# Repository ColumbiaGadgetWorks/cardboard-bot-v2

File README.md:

# Cardboard Bot v2

Cardboard battlebots for Columbia Gadget Works, built on the Seeed XIAO ESP32-C3.

- Each robot hosts its own Wi-Fi access point. You drive it from a phone browser,
  with an optional Bluetooth gamepad (DS4 and others) through the browser's Gamepad API.
- Firmware is flashed from a browser-based web flasher on GitHub Pages; updates go over the
  robot's own AP.
- The board runs from a 2S or 3S LiPo on a screw terminal, drives two gearmotors through two
  DRV8870s, and has three 3-pin outputs for ESCs or servos (two weapon ESCs by default).

| Folder | Contents |
|---|---|
| [`hardware/`](hardware/) | KiCad 7 main board, rev B (2S/3S LiPo, 60 × 46 mm): schematic, PCB, JLCPCB fab files and the generator scripts |
| [`firmware/`](firmware/) | ESP-IDF firmware for the XIAO ESP32-C3, including the phone controller page |
| [`site/`](site/) | Web flasher, published to GitHub Pages with every firmware build |

**Flash a robot:** <https://columbiagadgetworks.github.io/cardboard-bot-v2/> (desktop Chrome or Edge, or Firefox 151+).
**Drive it:** join the robot's Wi-Fi (`CGW-<name>`) and open **https://192.168.4.1** on the phone.

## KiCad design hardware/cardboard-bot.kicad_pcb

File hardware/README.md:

# Cardboard Bot v2 – main board (rev B)

60 × 46 mm, 2-layer, 2 oz copper, for a **2S or 3S LiPo** on a screw terminal. JLCPCB assembles
the SMD parts on the top side; CGW hand-solders the through-hole parts. Nothing goes on the back.

| What | Where |
|---|---|
| Schematic (PDF) | `docs/schematic.pdf` |
| KiCad 7 project | `cardboard-bot.kicad_pro` / `.kicad_sch` / `.kicad_pcb` |
| JLCPCB upload files | `fab/` (gerber zip, BOM, CPL) |
| Hand-solder list | `fab/cardboard-bot-v2-revB-hand-solder.csv` |
| Part-number check list | `docs/BOM_CHECK.md` |

## What's on the board

Parts were picked for JLC stock: Basic or no-fee Preferred parts wherever JLC has one, otherwise a
well-stocked Extended part (stock checked 28 Oct 2026, see `docs/BOM_CHECK.md`). Everything on the
battery side is rated above 3S (12.6 V full).

- **Battery input:** 5.08 mm screw terminal J1 (top-left), then a **20 A mini blade fuse**, then two
  wire pads for an off-board **power switch** (10 A+ DC, 18 AWG). A unidirectional **SMAJ13A**
  clamps spikes at about 21 V; a reversed battery makes it conduct and blows the fuse.
- **ESC power:** two 5.08 mm screw terminals on the right edge (ESC 1, ESC 2), after the fuse
  and switch, with a 470 µF / 25 V bulk capacitor next to them.
- **Drive:** two **DRV8870** H-bridges (6.5–45 V, 3.6 A peak), one per motor, each next to its
  3.5 mm motor terminal: **LEFT MOTOR** on the left edge, **RIGHT MOTOR** on the right edge.
  0.1 Ω sense resistors and VREF = 2.53 V limit each motor to about 2.5 A. The DRV8870 stops
  below about 6.5 V, so on 2S the drive cuts out near empty (the firmware stops it at 3.0 V/cell anyway).
- **5 V:** TPS54202 buck (28 V max in) behind a Schottky diode and a 470 µF / 25 V hold-up
  capacitor, so ESC current spikes can't reset the ESP32. A second Schottky feeds the XIAO, so
  plugging in its USB while the robot is on is safe.
- **Outputs:** three 3-pin headers (GND / V+ / SIG): OUT1 (GPIO10), OUT2 (GPIO20), OUT3 (GPIO21).
  V+ is 5 V through a Schottky per output, so an ESC's BEC can't back-feed the board. The
  firmware default is two weapon ESCs on OUT1 and OUT2. OUT3's pin carries the ESP32 boot
  messages for a moment at power-up, so use it for a servo rather than an ESC.
- **Pull-downs:** 10k on all four motor inputs and all three outputs, so the motors coast and the
  ESCs see "off" while the ESP32 resets and boots (its pins float until the firmware starts).
- **Battery sense:** pack ÷ 6 (100k / 20k) on GPIO3, so 3S full (12.6 V) reads 2.1 V. The
  firmware detects 2S / 3S at power-on.
- **Status LED:** pads for one LED cut from a WS2812B strip (5 V, 60 LED/m, 10 mm), powered
  through a 1N4148W (about 4.2 V) so the 3.3 V data line is read reliably.
- **I2C header** J2 (GND, 3V3, SCL, SDA) with pull-ups, for add-ons.
- **Mounting:** two M3 holes (left middle, bottom right).

### XIAO pin map

| XIAO | GPIO | Use |
|---|---|---|
| D0 | 2 | SDA (I2C header) |
| D1 | 3 | Battery sense (pack ÷ 6) |
| D2 / D3 | 4 / 5 | Left DRV8870 IN1 / IN2 |
| D4 / D5 | 6 / 7 | Right DRV8870 IN1 / IN2 |
| D6 | 21 | OUT3 – also UART TX at boot |
| D7 | 20 | OUT2 |
| D8 | 8 | SCL (I2C header) |
| D9 | 9 | RGB LED data (BOOT button pin) |
| D10 | 10 | OUT1 |

GPIO2, GPIO8 and GPIO9 are strapping pins. They only carry signals that idle high at boot
(I2C pull-ups, and the BOOT button with the LED data line), so the chip always boots normally.
None of them has a pull-down.

## Before ordering – check these

1. **LCSC part numbers and stock.** Go through `docs/BOM_CHECK.md` on jlcpcb.com/parts.
2. **JLC placement preview.** `ROT_FIX` in `gen/fab.py` holds the corrections from rev A's preview.
   The DRV8870 (U3, U4) is new: check its pin-1 dot against the silkscreen triangle and add a
   correction if it's turned. JLC flags U1's footprint name (TSOT-23-6 vs SOT-23-6); the pads match.
3. **Values to sanity-check against the datasheets:** DRV8870 VREF / sense resistor (2.5 A limit),
   TPS54202 output inductor (10 µH) and capacitors (2 × 22 µF).
4. **Assembly:**
   - **LED strip:** cut one LED from the strip on the cut lines. Tin the three J10 pads, lay the
     piece on them with its DIN end on the +5V / DIN / GND pads (arrow pointing away), and heat
     each strip pad from the top. Strips differ: check the +5V / DIN / GND order matches the
     silkscreen first, or wire it with three short wires instead.
   - **Power switch:** mount it in the cardboard and run two 18 AWG wires to the SW1 pads.
   - **Battery:** use 14–16 AWG leads into J1. The 5.08 mm terminals are rated about 16 A; for
     bigger weapons, solder the battery leads instead.

## Regenerating

Everything is generated from `gen/circuit.py` (parts, LCSC numbers, nets).
You need KiCad 7 (`kicad-cli` and its Python module), python3-numpy and python3-pil.

```sh
python3 gen/gen_footprints.py          # lib/cgw.pretty (XIAO socket, LED strip pads, CGW logos)
python3 gen/gen_sch.py                 # schematic + lib/cgw.kicad_sym
kicad-cli sch export pdf -o docs/schematic.pdf cardboard-bot.kicad_sch
PY=/usr/bin/python3.12
$PY gen/gen_pcb.py                     # outline, placement, silkscreen, pre-routed power copper, router keepouts
$PY gen/route.py --stage zones         # GND pours (both layers) + solid power pours
$PY gen/fixroute.py                    # A* grid router for every remaining connection (rips up and retries)
$PY gen/route.py --stage stitch        # GND stitching vias
$PY gen/islands.py                     # ties any leftover GND pour islands
$PY gen/gnd_check.py                   # lists GND copper cut off from the main cluster (DRC won't say where)
(cd gen && $PY tie_pad.py --min 3 REF PAD)   # route a stranded pad to a GND via, if gnd_check finds one
$PY gen/route.py --stage drop-keepouts && $PY gen/route.py --stage fill
$PY gen/silk.py                        # redraw labels only (safe on a routed board)
$PY gen/drc.py                         # DRC summary
python3 gen/fab.py                     # fab/ outputs; BOM and CPL designators are cross-checked
bash gen/render.sh                     # PNG previews
```

`gen_pcb.py` builds the board from scratch, which wipes the routing. A full re-route takes a few
minutes. After small changes it is usually easier to edit `cardboard-bot.kicad_pcb` in KiCad directly.
`gen/patch_prewire.py NET,...` re-applies the fixed copper of individual nets on a routed board.

This board was routed with `gen/fixroute.py`. `gen/route.py` can also run Freerouting if you have
Java and `freerouting.jar` installed (`route.py` with no arguments).

## Preview

| Top | Bottom (mirrored) |
|---|---|
|  |  |

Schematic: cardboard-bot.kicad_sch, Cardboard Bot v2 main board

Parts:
C1, C2: 470uF 25V; CP_Radial_D8.0mm_P3.50mm; MPN 470uF 25V radial, 8 mm dia, 3.5 mm pitc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
C3, C9, C14, C16: 10uF; C_0805_2012Metric; MPN CL21A106KAYNNNE; LCSC C15850
C4, C5, C10, C11, C12, C13, C15, C17, C18: 100nF; C_0603_1608Metric; MPN CC0603KRX7R9BB104; LCSC C14663
C6, C7: 22uF; C_0805_2012Metric; MPN CL21A226MAQNNNE; LCSC C45783
D1: SMAJ13A; D_SMA; MPN SMAJ13A; LCSC C19077533
D2: SS34; D_SMA; MPN SS34; LCSC C8678
D3: B5819W; D_SOD-123; MPN B5819W SL; LCSC C8598
D4, D5, D6: 1N5819WS; D_SOD-323; MPN 1N5819WS; LCSC C191023
D7: 1N4148W; D_SOD-123; MPN 1N4148W; LCSC C81598
F1: 20A mini blade; Fuseholder_Blade_Mini_Keystone_3568; MPN Mini blade holder (Keystone 3568 footpr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
J1: BATTERY; TerminalBlock_Phoenix_MKDS-1,5-2-5.08_1x02_P5.08mm_Horizont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; MPN 2P screw terminal 5.08mm (KF301), 2S or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
J2: I2C; PinSocket_1x04_P2.54mm_Vertical; MPN 1x4 female header 2.54
J3: LEFT MOTOR; TerminalBlock_Phoenix_PT-1,5-2-3.5-H_1x02_P3.50mm_Horizontal; MPN 2P screw terminal 3.5mm
J4: RIGHT MOTOR; TerminalBlock_Phoenix_PT-1,5-2-3.5-H_1x02_P3.50mm_Horizontal; MPN 2P screw terminal 3.5mm
J5: OUT1; PinHeader_1x03_P2.54mm_Vertical; MPN 1x3 male header 2.54
J6: OUT2; PinHeader_1x03_P2.54mm_Vertical; MPN 1x3 male header 2.54
J7: OUT3; PinHeader_1x03_P2.54mm_Vertical; MPN 1x3 male header 2.54
J8: ESC PWR 1; TerminalBlock_Phoenix_MKDS-1,5-2-5.08_1x02_P5.08mm_Horizont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; MPN 2P screw terminal 5.08mm (KF301)
J9: ESC PWR 2; TerminalBlock_Phoenix_MKDS-1,5-2-5.08_1x02_P5.08mm_Horizont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; MPN 2P screw terminal 5.08mm (KF301)
J10: LED STRIP; WS2812B_Strip_1LED; MPN 1 LED cut from a WS2812B strip: 5 V, 60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
L1: 10uH 2.35A; L_Cenker_CKCS4030; MPN FHD4020S-100MT; LCSC C602032
R1: 75k; R_0603_1608Metric; MPN 0603WAF7502T5E; LCSC C23242
R2, R9, R11, R12, R13, R14, R18, R19, R20: 10k; R_0603_1608Metric; MPN 0603WAF1002T5E; LCSC C25804
R3, R4: 4.7k; R_0603_1608Metric; MPN 0603WAF4701T5E; LCSC C23162
R5: 100k; R_0603_1608Metric; MPN 0603WAF1003T5E; LCSC C25803
R6: 20k; R_0603_1608Metric; MPN 0603WAF2002T5E; LCSC C4184
R7, R8: 0.1R; R_1206_3216Metric; MPN 1206W4F100LT5E; LCSC C25334
R10: 33k; R_0603_1608Metric; MPN 0603WAF3302T5E; LCSC C4216
R15, R16, R17: 1k; R_0603_1608Metric; MPN 0603WAF1001T5E; LCSC C21190
R21: 330R; R_0603_1608Metric; MPN 0603WAF3300T5E; LCSC C23138
SW1: POWER SW; SolderWire-0.75sqmm_1x02_P4.8mm_D1.25mm_OD2.3mm; MPN SPST rocker or toggle, 10 A+ at 16 V DC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
TP1: +3V3; TestPoint_Pad_D1.5mm
TP2: GND; TestPoint_Pad_D1.5mm
U1: TPS54202DDCR; TSOT-23-6; MPN TPS54202DDCR; LCSC C191884
U2: XIAO ESP32-C3; XIAO_Socket; MPN Seeed XIAO ESP32C3 + 2x 1x7 female head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
U3, U4: DRV8870DDAR; Texas_HTSOP-8-1EP_3.9x4.9mm_P1.27mm_EP2.95x4.9mm_Mask2.4x3.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; MPN DRV8870DDAR; LCSC C86590

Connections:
+3V3: C11.1, J2.2, R3.1, R4.1, R9.1, TP1.1, U2.12 (3V3)
+5V: C6.1, C7.1, D3.2 (A), D4.2 (A), D5.2 (A), D6.2 (A), D7.2 (A), L1.2, R1.1
+5V_XIAO: C9.1, C10.1, D3.1 (K), U2.14 (5V)
AIN1: R11.1, U2.3 (D2/GPIO4), U3.3 (IN1)
AIN2: R12.1, U2.4 (D3/GPIO5), U3.2 (IN2)
BAT+: F1.1, J1.1
BIN1: R13.1, U2.5 (D4/GPIO6), U4.3 (IN1)
BIN2: R14.1, U2.6 (D5/GPIO7), U4.2 (IN2)
BUCK_BST: C5.1, U1.6 (BOOT)
BUCK_FB: R1.2, R2.1, U1.4 (FB)
BUCK_SW: C5.2, L1.1, U1.2 (SW)
DRV_VREF: C13.1, R9.2, R10.1, U3.4 (VREF), U4.4 (VREF)
GND: C1.2, C2.2, C3.2, C4.2, C6.2, C7.2, C9.2, C10.2, C11.2, C12.2, C13.2, C14.2, C15.2, C16.2, C17.2, C18.2, D1.2 (A), J1.2, J2.1, J5.1, J6.1, J7.1, J8.2, J9.2, J10.3, R2.2, R6.2, R7.2, R8.2, R10.2, R11.2, R12.2, R13.2, R14.2, R18.2, R19.2, R20.2, TP2.1, U1.1 (GND), U2.13 (GND), U3.1 (GND), U3.9 (GND), U4.1 (GND), U4.9 (GND)
IO10: R15.1, R18.1, U2.11 (D10/GPIO10)
IO20: R16.1, R19.1, U2.8 (D7/GPIO20)
IO21: R17.1, R20.1, U2.7 (D6/GPIO21)
ISEN_L: R7.1, U3.7 (ISEN)
ISEN_R: R8.1, U4.7 (ISEN)
LED_DIN: J10.2, R21.2
LED_DIN3: R21.1, U2.10 (D9/GPIO9)
LED_VDD: C18.1, D7.1 (K), J10.1
MOTL_A: J3.1, U3.6 (OUT1)
MOTL_B: J3.2, U3.8 (OUT2)
MOTR_A: J4.1, U4.6 (OUT1)
MOTR_B: J4.2, U4.8 (OUT2)
OUT1_SIG: J5.3, R15.2
OUT1_VP: D4.1 (K), J5.2
OUT2_SIG: J6.3, R16.2
OUT2_VP: D5.1 (K), J6.2
OUT3_SIG: J7.3, R17.2
OUT3_VP: D6.1 (K), J7.2
SCL: J2.3, R4.2, U2.9 (D8/GPIO8)
SDA: J2.4, R3.2, U2.1 (D0/GPIO2)
VBAT_SNS: C12.1, R5.2, R6.1, U2.2 (D1/GPIO3)
VFUSE: F1.2, SW1.1 (A)
VHOLD: C2.1, C3.1, C4.1, D2.1 (K), U1.3 (VIN)
VSYS: C1.1, C14.1, C15.1, C16.1, C17.1, D1.1 (K), D2.2 (A), J8.1, J9.1, R5.1, SW1.2 (B), U3.5 (VM), U4.5 (VM)

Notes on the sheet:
1 Battery input (2S / 3S LiPo), 20 A blade fuse, power switch, surge clamp, ESC power
2 Hold-up + 5 V buck (TPS54202), XIAO feed
3 XIAO ESP32-C3, I2C, battery sense
4 2x DRV8870 drive, 2.5 A current limit
5 PWM outputs (ESC or servo)
6 RGB status LED (WS2812B strip piece)
Power flags (ERC)
Cardboard Bot v2 main board - rev B - Columbia Gadget Works
Generated from hardware/gen/circuit.py (do not hand-edit; edit circuit.py and regenerate).
All connections are made by net labels at pin ends.
Power: 2S or 3S LiPo on J1. Everything on VSYS is rated for 3S (12.6 V) with margin; SMAJ13A clamps spikes at about 21 V.
XIAO pins: D0 SDA(GPIO2) D1 VBAT/6(GPIO3) D2-D3 left DRV8870 IN1/IN2 D4-D5 right DRV8870 IN1/IN2 D6 OUT3(GPIO21) D7 OUT2(GPIO20) D8 SCL(GPIO8) D9 LED(GPIO9) D10 OUT1(GPIO10)
10k pull-downs on every motor input and output keep motors and ESCs off while the ESP32 boots.

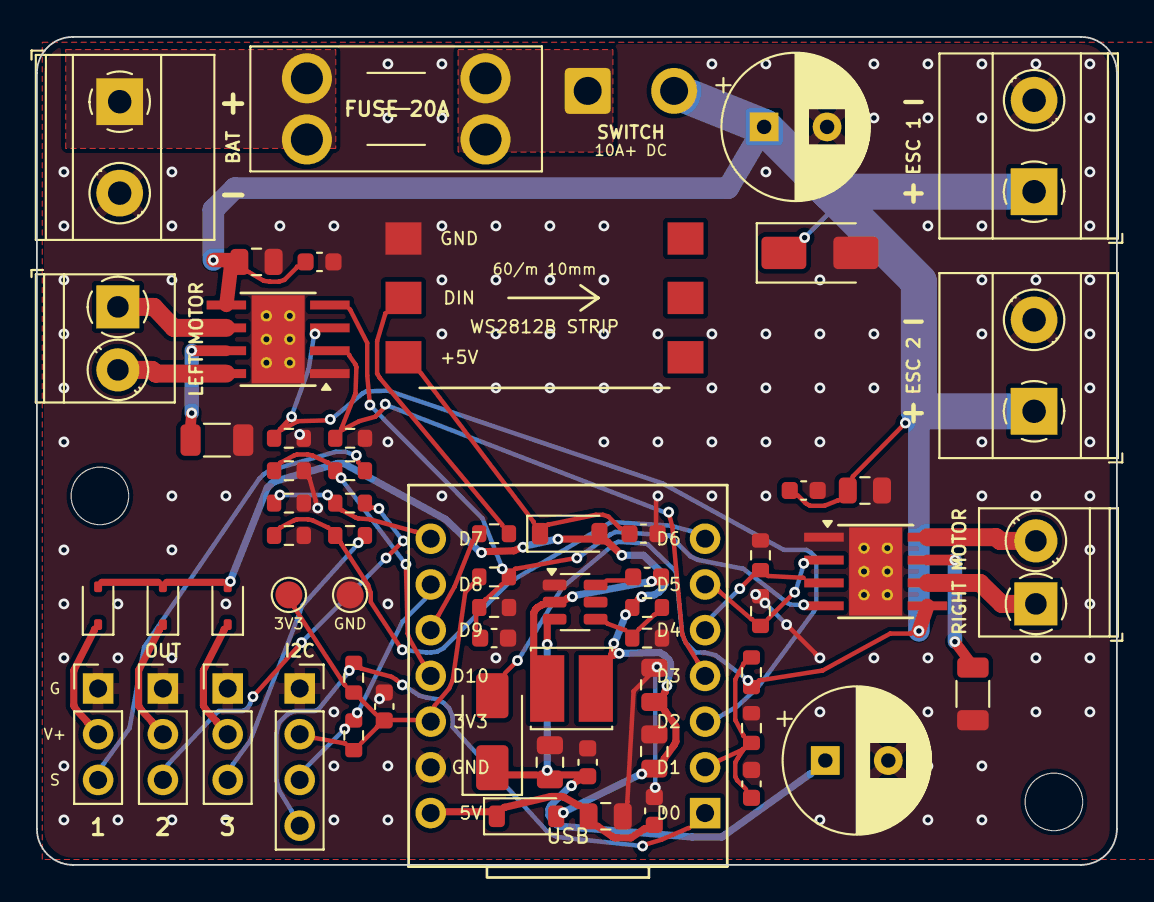
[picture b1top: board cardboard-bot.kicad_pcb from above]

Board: 2 copper layers, 60.0 x 46.0 mm, 67 parts (1 on the bottom side), 37 nets.

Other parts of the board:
H1, H2: MountingHole_3.2mm_M3
LOGO2: CGW_Logo

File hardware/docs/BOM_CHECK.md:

# LCSC part check (rev B)

Stock, price and library type are from a JLC parts snapshot taken **28 Oct 2026**:
- [yaqwsx/jlcparts](https://github.com/yaqwsx/jlcparts) for stock and price
- [CDFER/jlcpcb-parts-database](https://github.com/CDFER/jlcpcb-parts-database) for the Basic and Preferred lists

They change daily. Open each part on <https://jlcpcb.com/parts> before ordering and tick it off.

- **Basic** and **Preferred** parts have no feeder fee.
- Each **Extended** line usually adds about $3 per order.
- JLC stocks no Basic motor driver, buck converter or power inductor, so those three are
  well-stocked Extended parts. There is no Basic TVS with a stand-off above 3S, so D1 is the
  SMAJ13A (Preferred).

## 3S ratings

| Part | Rating | On the 12.6 V rail |
|---|---|---|
| DRV8870 (U3, U4) | 45 V | motor supply |
| TPS54202 (U1) | 28 V | buck input |
| SMAJ13A (D1) | 13 V stand-off, clamps 21.5 V | surge clamp |
| SS34 (D2) | 40 V | hold-up diode |
| 10 µF 0805 (C3, C14, C16) | 25 V | bulk ceramics |
| 100 nF 0603 | 50 V | decoupling |
| 470 µF radials (C1, C2) | 25 V | bulk, hand-soldered |

## Check by hand before paying

- **U3, U4 DRV8870DDAR:** pin 1 GND, 2 IN2, 3 IN1, 4 VREF, 5 VM, 6 OUT1, 7 ISEN, 8 OUT2, pad GND
  (TI SLVSCY9). Check the pin-1 dot in JLC's placement preview; this part is new on rev B.
- **Rotations:** `ROT_FIX` in `gen/fab.py` holds the rev A corrections (U1 TPS54202 is the same part).
- **U1 footprint warning:** JLC lists the TPS54202DDCR as SOT-23-6; the board uses KiCad's TSOT-23-6,
  which is TI's DDC land pattern (same pin pitch and pad positions). The warning is about the name only.

## Assembled by JLCPCB (top side)

| LCSC | Value | MPN | Footprint | Qty/board | Designators | JLC library | JLC stock | Unit price |
|---|---|---|---|---|---|---|---|---|
| C15850 | 10uF | CL21A106KAYNNNE | C_0805_2012Metric | 4 | C14, C16, C3, C9 | Basic | 3,710,191 | $0.0692 |
| C14663 | 100nF | CC0603KRX7R9BB104 | C_0603_1608Metric | 9 | C10, C11, C12, C13, C15, C17, C18, C4, C5 | Basic | 50,349,394 | $0.0141 |
| C45783 | 22uF | CL21A226MAQNNNE | C_0805_2012Metric | 2 | C6, C7 | Basic | 3,360,923 | $0.2384 |
| C19077533 | SMAJ13A | SMAJ13A | D_SMA | 1 | D1 | Preferred (no fee) | 45,855 | $0.0382 |
| C8678 | SS34 | SS34 | D_SMA | 1 | D2 | Basic | 4,004,526 | $0.0351 |
| C8598 | B5819W | B5819W SL | D_SOD-123 | 1 | D3 | Basic | 384,842 | $0.0284 |
| C191023 | 1N5819WS | 1N5819WS | D_SOD-323 | 3 | D4, D5, D6 | Basic | 4,286,668 | $0.0139 |
| C81598 | 1N4148W | 1N4148W | D_SOD-123 | 1 | D7 | Basic | 4,633,707 | $0.0124 |
| C602032 | 10uH 2.35A | FHD4020S-100MT | L_Cenker_CKCS4030 | 1 | L1 | Extended ($3 fee) | 99,381 | $0.0640 |
| C23242 | 75k | 0603WAF7502T5E | R_0603_1608Metric | 1 | R1 | Basic | 1,012,894 | $0.0021 |
| C4216 | 33k | 0603WAF3302T5E | R_0603_1608Metric | 1 | R10 | Basic | 3,644,037 | $0.0021 |
| C21190 | 1k | 0603WAF1001T5E | R_0603_1608Metric | 3 | R15, R16, R17 | Basic | 24,277,749 | $0.0020 |
| C25804 | 10k | 0603WAF1002T5E | R_0603_1608Metric | 9 | R11, R12, R13, R14, R18, R19, R2, R20, R9 | Basic | 32,380,385 | $0.0052 |
| C23138 | 330R | 0603WAF3300T5E | R_0603_1608Metric | 1 | R21 | Basic | 3,527,043 | $0.0022 |
| C23162 | 4.7k | 0603WAF4701T5E | R_0603_1608Metric | 2 | R3, R4 | Basic | 19,500,720 | $0.0028 |
| C25803 | 100k | 0603WAF1003T5E | R_0603_1608Metric | 1 | R5 | Basic | 19,748,113 | $0.0031 |
| C4184 | 20k | 0603WAF2002T5E | R_0603_1608Metric | 1 | R6 | Basic | 7,868,484 | $0.0022 |
| C25334 | 0.1R | 1206W4F100LT5E | R_1206_3216Metric | 2 | R7, R8 | Basic | 552,267 | $0.0091 |
| C191884 | TPS54202DDCR | TPS54202DDCR | TSOT-23-6 | 1 | U1 | Extended ($3 fee) | 299,988 | $0.1786 |
| C86590 | DRV8870DDAR | DRV8870DDAR | Texas_HTSOP-8-1EP_3.9x4.9mm_P1.27mm_EP2.95x4.9mm_Mask2.4x3.1mm_ThermalVias | 2 | U3, U4 | Extended ($3 fee) | 158,471 | $0.3456 |

**20 BOM lines.** Basic: 16, Preferred: 1, Extended: 3 (about $9 in feeder fees per order, if JLC charges them).
Parts cost about **$2.06 per board** at single-unit prices, so about $62 for 30 boards, before JLC's setup and assembly fees.

## Hand-soldered by CGW

| Designator | Part | Notes |
|---|---|---|
| J1 | BATTERY | 2P screw terminal 5.08mm (KF301), 2S or 3S LiPo |
| F1 | 20A mini blade | Mini blade holder (Keystone 3568 footprint) |
| SW1 | POWER SW | SPST rocker or toggle, 10 A+ at 16 V DC, panel mount, 18 AWG silicone wire |
| C1 | 470uF 25V | 470uF 25V radial, 8 mm dia, 3.5 mm pitch, low ESR |
| J8 | ESC PWR 1 | 2P screw terminal 5.08mm (KF301) |
| J9 | ESC PWR 2 | 2P screw terminal 5.08mm (KF301) |
| C2 | 470uF 25V | 470uF 25V radial, 8 mm dia, 3.5 mm pitch, low ESR |
| U2 | XIAO ESP32-C3 | Seeed XIAO ESP32C3 + 2x 1x7 female header |
| J2 | I2C | 1x4 female header 2.54 |
| J3 | LEFT MOTOR | 2P screw terminal 3.5mm |
| J4 | RIGHT MOTOR | 2P screw terminal 3.5mm |
| J5 | OUT1 | 1x3 male header 2.54 |
| J6 | OUT2 | 1x3 male header 2.54 |
| J7 | OUT3 | 1x3 male header 2.54 |
| J10 | LED STRIP | 1 LED cut from a WS2812B strip: 5 V, 60 LED/m, 10 mm wide, pads +5V/DIN/GND |

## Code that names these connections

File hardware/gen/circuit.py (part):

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         pins={"1": BAT, "2": GND}))
add(dict(ref="F1", sym="Device:Fuse", value="20A mini blade", fp="Fuse:Fuseholder_Blade_Mini_Keystone_3568",
         lcsc="", mpn="Mini blade holder (Keystone 3568 footprint)", place="hand", block="power",
         pins={"1": BAT, "2": VFUSE}))
# The power switch carries the full battery current, so it's an off-board panel switch on two
# 0.75 mm2 (18 AWG) wire pads (fuse output -> VSYS).
add(dict(ref="SW1", sym="Switch:SW_SPST", value="POWER SW", fp="Connector_Wire:SolderWire-0.75sqmm_1x02_P4.8mm_D1.25mm_OD2.3mm",
         lcsc="", mpn="SPST rocker or toggle, 10 A+ at 16 V DC, panel mount, 18 AWG silicone wire",
         place="hand", block="power", pins={"1": VFUSE, "2": VSYS}))
# 13 V stand-off (3S is 12.6 V full), clamps 21.5 V: below the buck's 28 V and the 25 V capacitors.
# Unidirectional, so a reversed battery forward-biases it and blows the fuse.
add(dict(ref="D1", sym="Device:D_Zener", value="SMAJ13A", fp="Diode_SMD:D_SMA",
         lcsc="C19077533", mpn="SMAJ13A", verified=True, place="jlc", block="power",
         pins={"1": VSYS, "2": GND}))
add(CP("C1", "470uF 25V", VSYS, GND, fp=CP8, mpn=CP470_NOTE, place="hand", block="power"))
add(dict(ref="J8", sym="Connector_Generic:Conn_01x02", value="ESC PWR 1", fp=TERM508,
         lcsc="", mpn="2P screw terminal 5.08mm (KF301)", place="hand", block="power", pins={"1": VSYS, "2": GND}))
add(dict(ref="J9", sym="Connector_Generic:Conn_01x02", value="ESC PWR 2", fp=TERM508,
         lcsc="", mpn="2P screw terminal 5.08mm (KF301)", place="hand", block="power", pins={"1": VSYS, "2": GND}))

# ---------------------------------------------------------------------------
# 2. 5 V buck with hold-up, XIAO feed
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# TPS54202: 4.5-28 V in; EN floats = enabled (internal pull-up)
add(dict(ref="U1", sym="Regulator_Switching:TPS54202DDC", value="TPS54202DDCR", fp="Package_TO_SOT_SMD:TSOT-23-6",
         lcsc="C191884", mpn="TPS54202DDCR", verified=True, place="jlc", block="buck",
         pins={"1": GND, "2": "BUCK_SW", "3": VHOLD, "4": "BUCK_FB", "5": None, "6": "BUCK_BST"}))
add(C("C5", "100nF", "BUCK_BST", "BUCK_SW", block="buck", **C100N))
add(dict(ref="L1", sym="Device:L", value="10uH 2.35A", fp="Inductor_SMD:L_Cenker_CKCS4030",
         lcsc="C602032", mpn="FHD4020S-100MT", verified=True, place="jlc", block="buck",
         pins={"1": "BUCK_SW", "2": V5}))
add(R("R1", "75k", V5, "BUCK_FB", lcsc="C23242", mpn="0603WAF7502T5E", verified=True, block="buck"))   # 0.596 V x (1 + 75/10) = 5.07 V
add(R("R2", "10k", "BUCK_FB", GND, block="buck", **R10K))
add(C("C6", "22uF", V5, GND, fp=F0805C, block="buck", **C22U))
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# ---------------------------------------------------------------------------
add(dict(ref="U2", sym="cgw:XIAO_ESP32C3", value="XIAO ESP32-C3", fp="cgw:XIAO_Socket",
         lcsc="", mpn="Seeed XIAO ESP32C3 + 2x 1x7 female header", place="hand", block="mcu",
         pins={"1": "SDA",        # D0 GPIO2  (strap, pulled up)
               "2": "VBAT_SNS",   # D1 GPIO3  battery / 6
               "3": "AIN1",       # D2 GPIO4  left motor
               "4": "AIN2",       # D3 GPIO5
               "5": "BIN1",       # D4 GPIO6  right motor
               "6": "BIN2",       # D5 GPIO7
               "7": "IO21",       # D6 GPIO21 OUT3 (ROM boot log for a moment at power-up)
               "8": "IO20",       # D7 GPIO20 OUT2
               "9": "SCL",        # D8 GPIO8  (strap, pulled up)
               "10": "LED_DIN3",  # D9 GPIO9  RGB LED + BOOT button
               "11": "IO10",      # D10 GPIO10 OUT1
               "12": V3, "13": GND, "14": V5_XIAO}))
add(R("R3", "4.7k", V3, "SDA", lcsc="C23162", mpn="0603WAF4701T5E", verified=True, block="mcu"))
add(R("R4", "4.7k", V3, "SCL", lcsc="C23162", mpn="0603WAF4701T5E", verified=True, block="mcu"))
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add(dict(ref="J2", sym="Connector_Generic:Conn_01x04", value="I2C", fp="Connector_PinSocket_2.54mm:PinSocket_1x04_P2.54mm_Vertical",
         lcsc="", mpn="1x4 female header 2.54", place="hand", block="mcu",
         pins={"1": GND, "2": V3, "3": "SCL", "4": "SDA"}))
# Battery voltage on GPIO3 (ADC1 ch3): VSYS / 6 -> 2.1 V at 12.6 V (3S full)
add(R("R5", "100k", VSYS, "VBAT_SNS", block="mcu", **R100K))
add(R("R6", "20k", "VBAT_SNS", GND, block="mcu", **R20K))
add(C("C12", "100nF", "VBAT_SNS", GND, block="mcu", **C100N))
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        ("U4", "BIN1", "BIN2", "MOTR_A", "MOTR_B", "ISEN_R", "R8", "C16", "C17", "J4", "RIGHT MOTOR")):
    add(dict(ref=u, sym="Driver_Motor:DRV8870DDA", value=DRV, fp=DRV_FP,
             lcsc="C86590", mpn=DRV, verified=True, place="jlc", block="drive",
             pins={"1": GND, "2": b, "3": a, "4": "DRV_VREF", "5": VSYS, "6": oa, "7": isen, "8": ob, "9": GND}))
    add(R(rs, "0.1R", isen, GND, fp="Resistor_SMD:R_1206_3216Metric", lcsc="C25334",
          mpn="1206W4F100LT5E", verified=True, block="drive"))
    add(C(cb, "10uF", VSYS, GND, fp=F0805C, block="drive", **C10U))
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# WS2812B strip LED run from 5 V minus a diode (~4.2 V), so the ESP32's 3.3 V data meets VIH = 0.7 x VDD
add(dict(ref="D7", sym="Device:D", value="1N4148W", fp="Diode_SMD:D_SOD-123",
         lcsc="C81598", mpn="1N4148W", verified=True, place="jlc", block="led",
         pins={"1": "LED_VDD", "2": V5}))
add(R("R21", "330R", "LED_DIN3", "LED_DIN", block="led", **R330))
# One LED cut from a WS2812B strip, laid flat on the board and soldered to three pads at its DIN end
add(dict(ref="J10", sym="Connector_Generic:Conn_01x03", value="LED STRIP", fp="cgw:WS2812B_Strip_1LED",
         lcsc="", mpn="1 LED cut from a WS2812B strip: 5 V, 60 LED/m, 10 mm wide, pads +5V/DIN/GND",
         place="hand", block="led", pins={"1": "LED_VDD", "2": "LED_DIN", "3": GND}))
add(C("C18", "100nF", "LED_VDD", GND, block="led", **C100N))

# Power flags for ERC (nets driven only by passive parts)
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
